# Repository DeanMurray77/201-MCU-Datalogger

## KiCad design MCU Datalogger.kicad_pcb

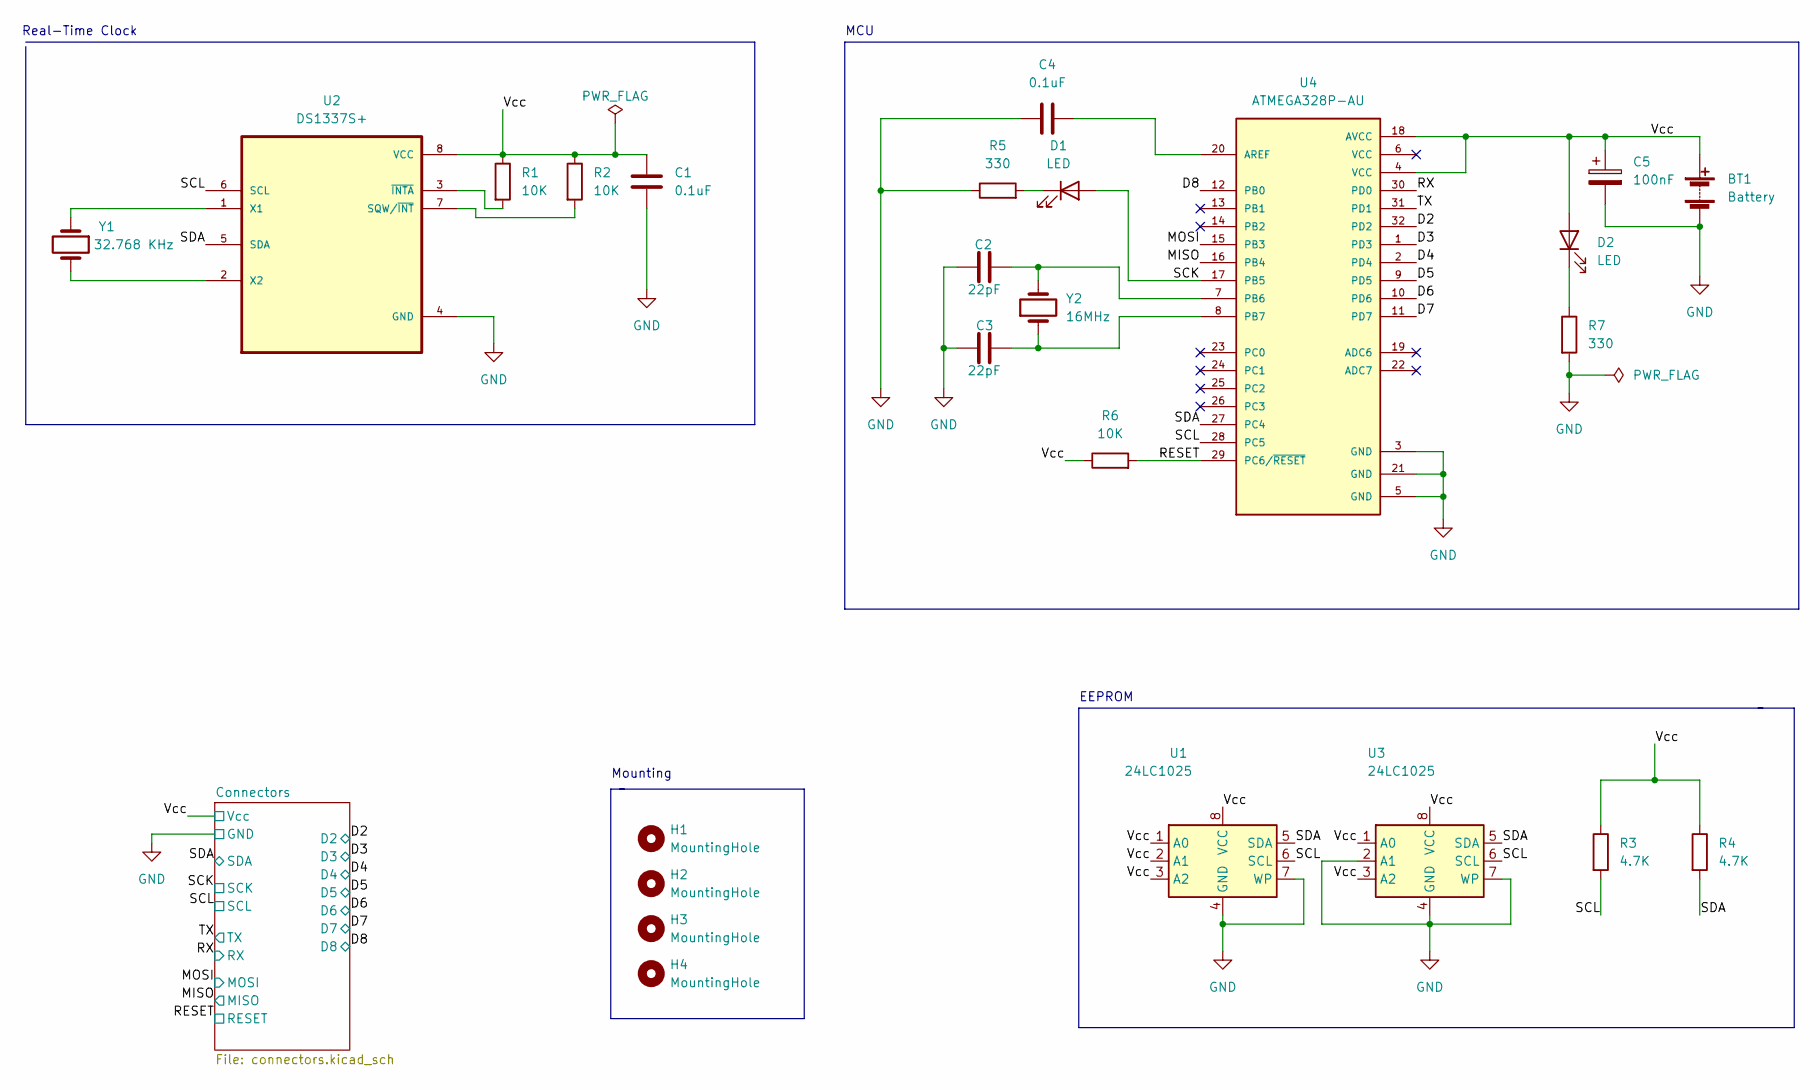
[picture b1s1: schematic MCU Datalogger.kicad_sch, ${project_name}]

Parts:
BT1: Battery; PinHeader_1x02_P2.54mm_Vertical
C1, C4: 0.1uF; C_0805_2012Metric
C2, C3: 22pF; C_0805_2012Metric
C5: 100nF; C_0805_2012Metric
D1, D2: LED; LED_0805_2012Metric
H1, H2, H3, H4: MountingHole; MountingHole_2.1mm
R1, R2, R6: 10K; R_0805_2012Metric
R3, R4: 4.7K; R_0805_2012Metric
R5, R7: 330; R_0805_2012Metric
U1, U3: 24LC1025; SOIC-8_5.23x5.23mm_P1.27mm
U2: DS1337S+; SOIC127P600X175-8N
U4: ATMEGA328P-AU; QFP80P900X900X120-32N
Y1: 32.768 KHz; Crystal_SMD_5032-2Pin_5.0x3.2mm_HandSoldering
Y2: 16MHz; Crystal_SMD_5032-2Pin_5.0x3.2mm_HandSoldering

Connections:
/D2: U4.32 (PD2); also elsewhere on the board
/D3: U4.1 (PD3); also elsewhere on the board
/D4: U4.2 (PD4); also elsewhere on the board
/D5: U4.9 (PD5); also elsewhere on the board
/D6: U4.10 (PD6); also elsewhere on the board
/D7: U4.11 (PD7); also elsewhere on the board
/D8: U4.12 (PB0); also elsewhere on the board
/MISO: U4.16 (PB4); also elsewhere on the board
/MOSI: U4.15 (PB3); also elsewhere on the board
/RESET: R6.2, U4.29 (PC6/~RESET); also elsewhere on the board
/RX: U4.30 (PD0); also elsewhere on the board
/SCK: D1.2 (A), U4.17 (PB5); also elsewhere on the board
/SCL: R3.2, U1.6 (SCL), U2.6 (SCL), U3.6 (SCL), U4.28 (PC5); also elsewhere on the board
/SDA: R4.2, U1.5 (SDA), U2.5 (SDA), U3.5 (SDA), U4.27 (PC4); also elsewhere on the board
/TX: U4.31 (PD1); also elsewhere on the board
/Vcc: BT1.1 (+), C1.1, C5.1, D2.2 (A), R1.1, R2.1, R3.1, R4.1, R6.1, U1.1 (A0), U1.2 (A1), U1.3 (A2), U1.8 (VCC), U2.8 (VCC), U3.1 (A0), U3.3 (A2), U3.8 (VCC), U4.4 (VCC), U4.18 (AVCC); also elsewhere on the board
GND: BT1.2 (-), C1.2, C2.1, C3.1, C4.1, C5.2, R5.1, R7.2, U1.4 (GND), U1.7 (WP), U2.4 (GND), U3.2 (A1), U3.4 (GND), U3.7 (WP), U4.3 (GND), U4.5 (GND), U4.21 (GND); also elsewhere on the board
unnamed: C2.2, U4.7 (PB6), Y2.2
unnamed: C3.2, U4.8 (PB7), Y2.1
unnamed: C4.2, U4.20 (AREF)
unnamed: D1.1 (K), R5.2
unnamed: D2.1 (K), R7.1
unnamed: R1.2, U2.3 (~INTA)
unnamed: R2.2, U2.7 (SQW/~INT)
unnamed: U2.1 (X1), Y1.1
unnamed: U2.2 (X2), Y1.2

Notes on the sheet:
EEPROM
Mounting
MCU
Real-Time Clock

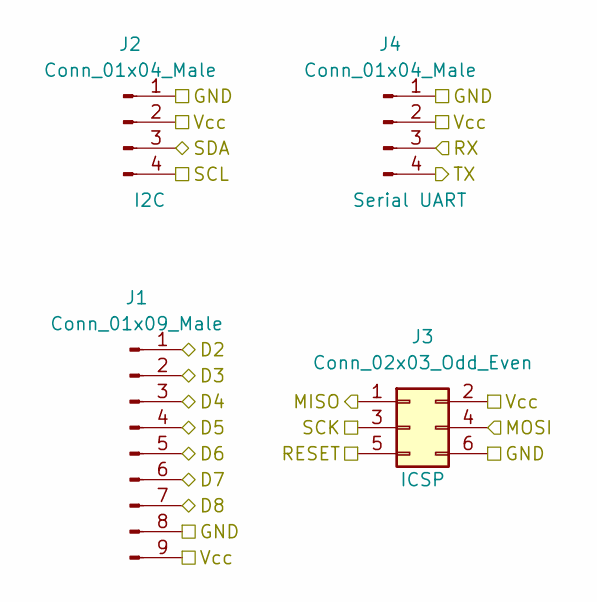
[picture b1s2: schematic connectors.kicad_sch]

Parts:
J1: Conn_01x09_Male; PinHeader_1x09_P2.54mm_Vertical
J2, J4: Conn_01x04_Male; PinHeader_1x04_P2.54mm_Vertical
J3: Conn_02x03_Odd_Even; PinHeader_2x03_P2.54mm_Vertical

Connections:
/D2: J1.1; also elsewhere on the board
/D3: J1.2; also elsewhere on the board
/D4: J1.3; also elsewhere on the board
/D5: J1.4; also elsewhere on the board
/D6: J1.5; also elsewhere on the board
/D7: J1.6; also elsewhere on the board
/D8: J1.7; also elsewhere on the board
/MISO: J3.1; also elsewhere on the board
/MOSI: J3.4; also elsewhere on the board
/RESET: J3.5; also elsewhere on the board
/RX: J4.3; also elsewhere on the board
/SCK: J3.3; also elsewhere on the board
/SCL: J2.4; also elsewhere on the board
/SDA: J2.3; also elsewhere on the board
/TX: J4.4; also elsewhere on the board
/Vcc: J1.9, J2.2, J3.2, J4.2; also elsewhere on the board
GND: J1.8, J2.1, J3.6, J4.1; also elsewhere on the board

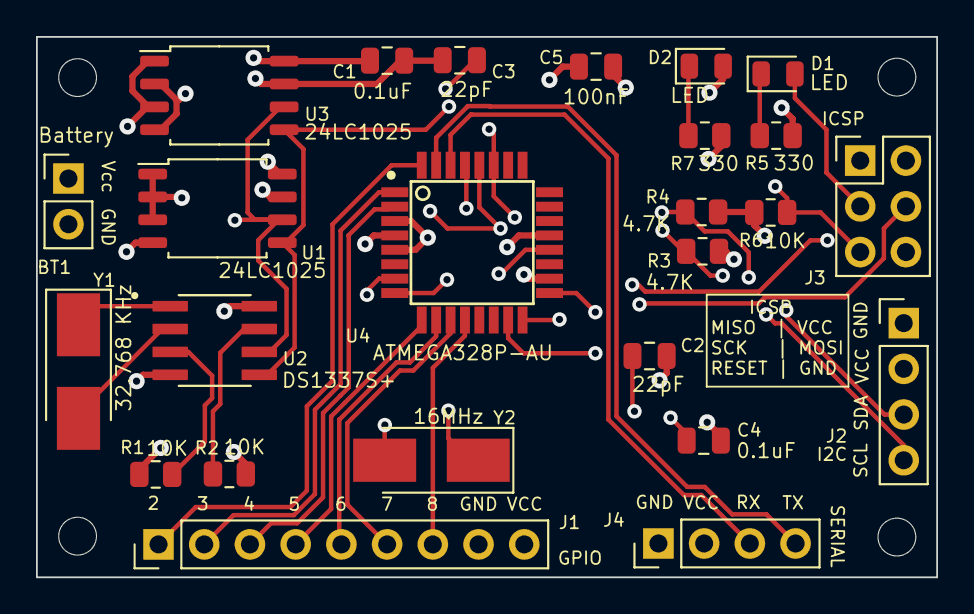
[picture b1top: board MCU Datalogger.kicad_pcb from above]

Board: 4 copper layers, 50.0 x 30.0 mm, 29 parts (0 on the bottom side), 26 nets.

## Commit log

2022-01-06 inital project and page setup
2022-01-08 Initial batch of symbols added
    Mounting holes, resistors, crystals, capacitors, LEDs, batteries and the like.
    Also imported the two parts from SnapEDA. I think all that is left is the headers.
2022-01-09 Add Connectors (in subpage)
    Created the sub page, added the connectors
2022-01-11 Arranged and annotated the symbols
2022-01-11 set values on the relevant symbols
2022-01-12 Import footprints. Associated the symbols to the footprints I want to use
2022-01-14 Part of the wiring done. On the main sheet. Still need to add some labels
2022-01-14 finished wiring of main sheet
2022-01-15 finished wiring everything up.
2022-01-16 added the GND and Vcc nets to the Power net class
2022-01-17 Add Comments and boxes around the different groups of components
2022-01-19 Setup the PCB Editor. Imported the footprints in from the schematic
2022-01-21 Did the initial add and positioning of footprints on the PCB
2022-01-22 beginning routing
2022-01-22 Fix schematic defect. SCK changed to SCL
2022-01-22 re-import the footprints into the PCB editor.
2022-01-25 More routing. Right before I decided to go back to the screwed up schematic and exactly match his errors
2022-01-26 Finished setting up the page/board settings & preferences
2022-01-26 Initial positioning of the footprints
2022-01-27 Routing in progress
2022-01-29 added some additional routing
2022-02-01 more routing
2022-02-02 more routing/wiring
2022-02-03 completed routing
2022-02-03 ready to start on the silk screen
2022-02-05 Post fixing the schematic for the missing vcc net and the pcb resulting changes
2022-02-05 add vcc to the wire going into the battery
2022-02-05 trying to merge master in to get the same vcc net
2022-02-05 finished upsizing the vcc tracks that didn't update automatically after I added the vcc net going into the battery
2022-02-05 silk screen squared away
2022-02-08 slight tweak of the copper traces
2022-02-09 Ready for manufacturing
2022-02-10 Added the missing 3D models
2022-02-11 rename gerber file directory and exclude it using git ignore
2022-02-11 add the 4-layer gerber directory to what is ignored by .gitignore
2022-02-12 beginning of 4layer routing
2022-02-12 more 4layer routing
2022-02-15 more routing. Fills
2022-02-17 routing good to go, copper fill good to go for 4layer version
2022-02-18 4-layer is ready for manufacuturing
2022-02-18 stop tracking gerber folder
2022-02-19 4-layer is all the way done
